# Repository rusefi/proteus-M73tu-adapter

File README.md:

# proteus-m73tu-adapter

Part of https://github.com/rusefi/rusefi/wiki/Proteus#adapters family

https://github.com/mck1117/proteus meets https://github.com/rusefi/rusefi/wiki/HOWTO-M73-v12-on-Proteus

V12 harness uses _TWO_ 134 pin connectors - one with BLACK plugs another with GREY plugs.

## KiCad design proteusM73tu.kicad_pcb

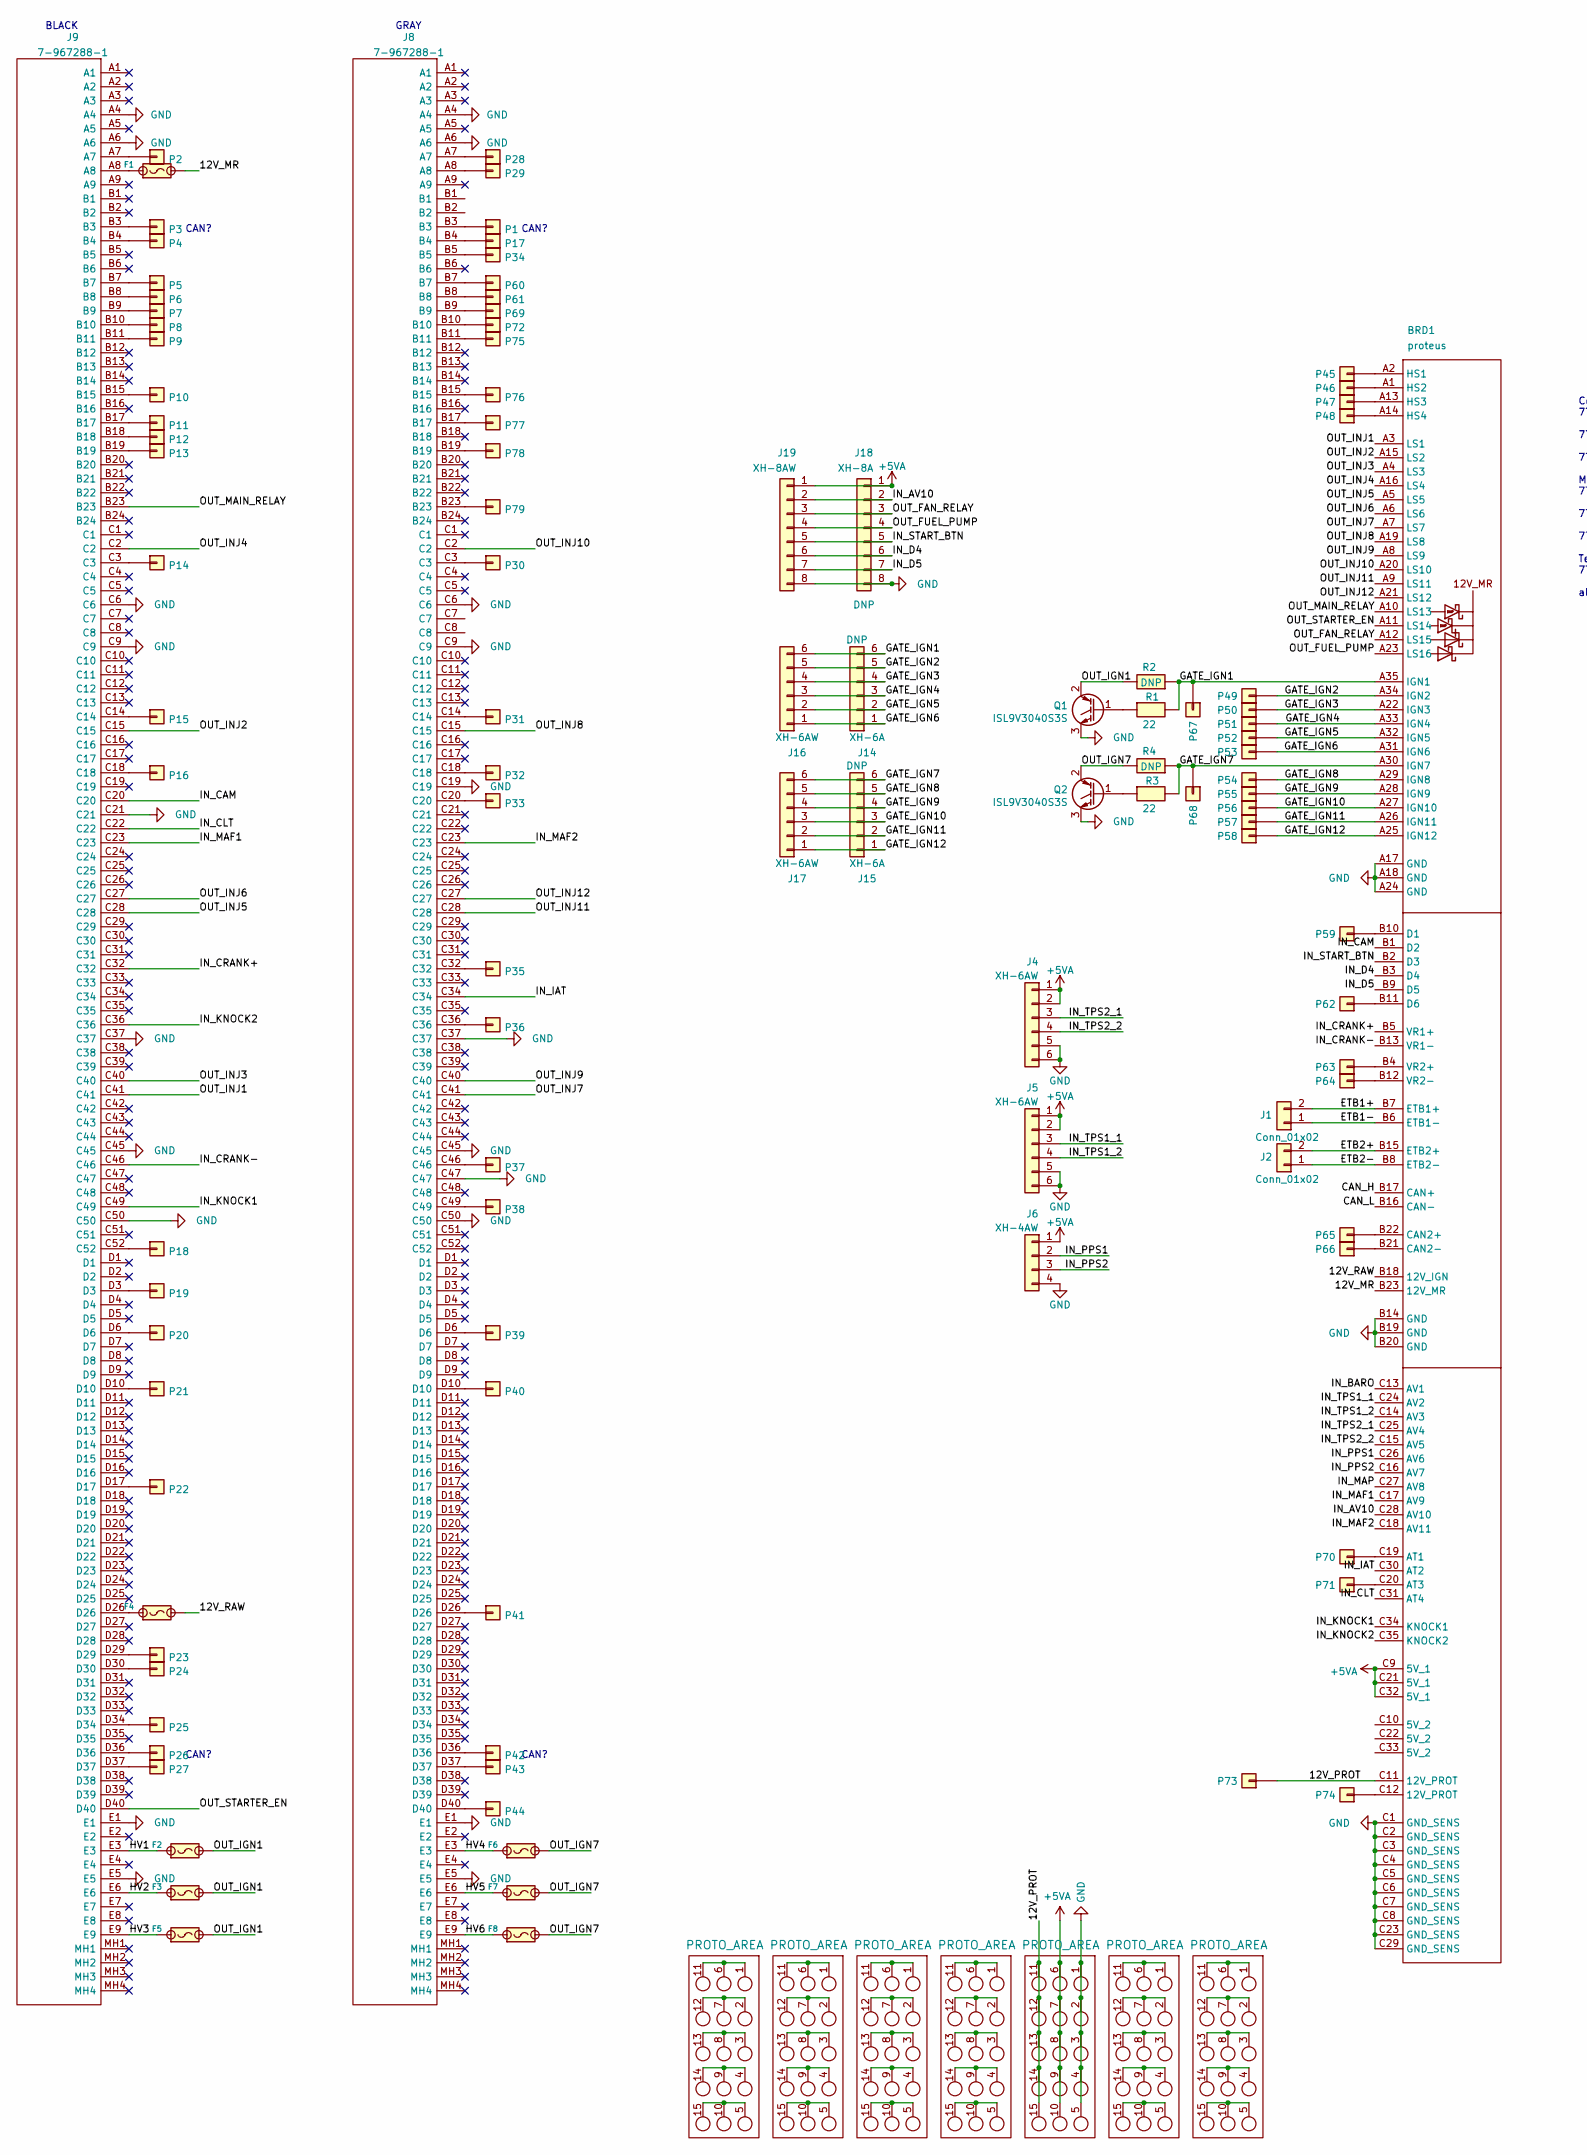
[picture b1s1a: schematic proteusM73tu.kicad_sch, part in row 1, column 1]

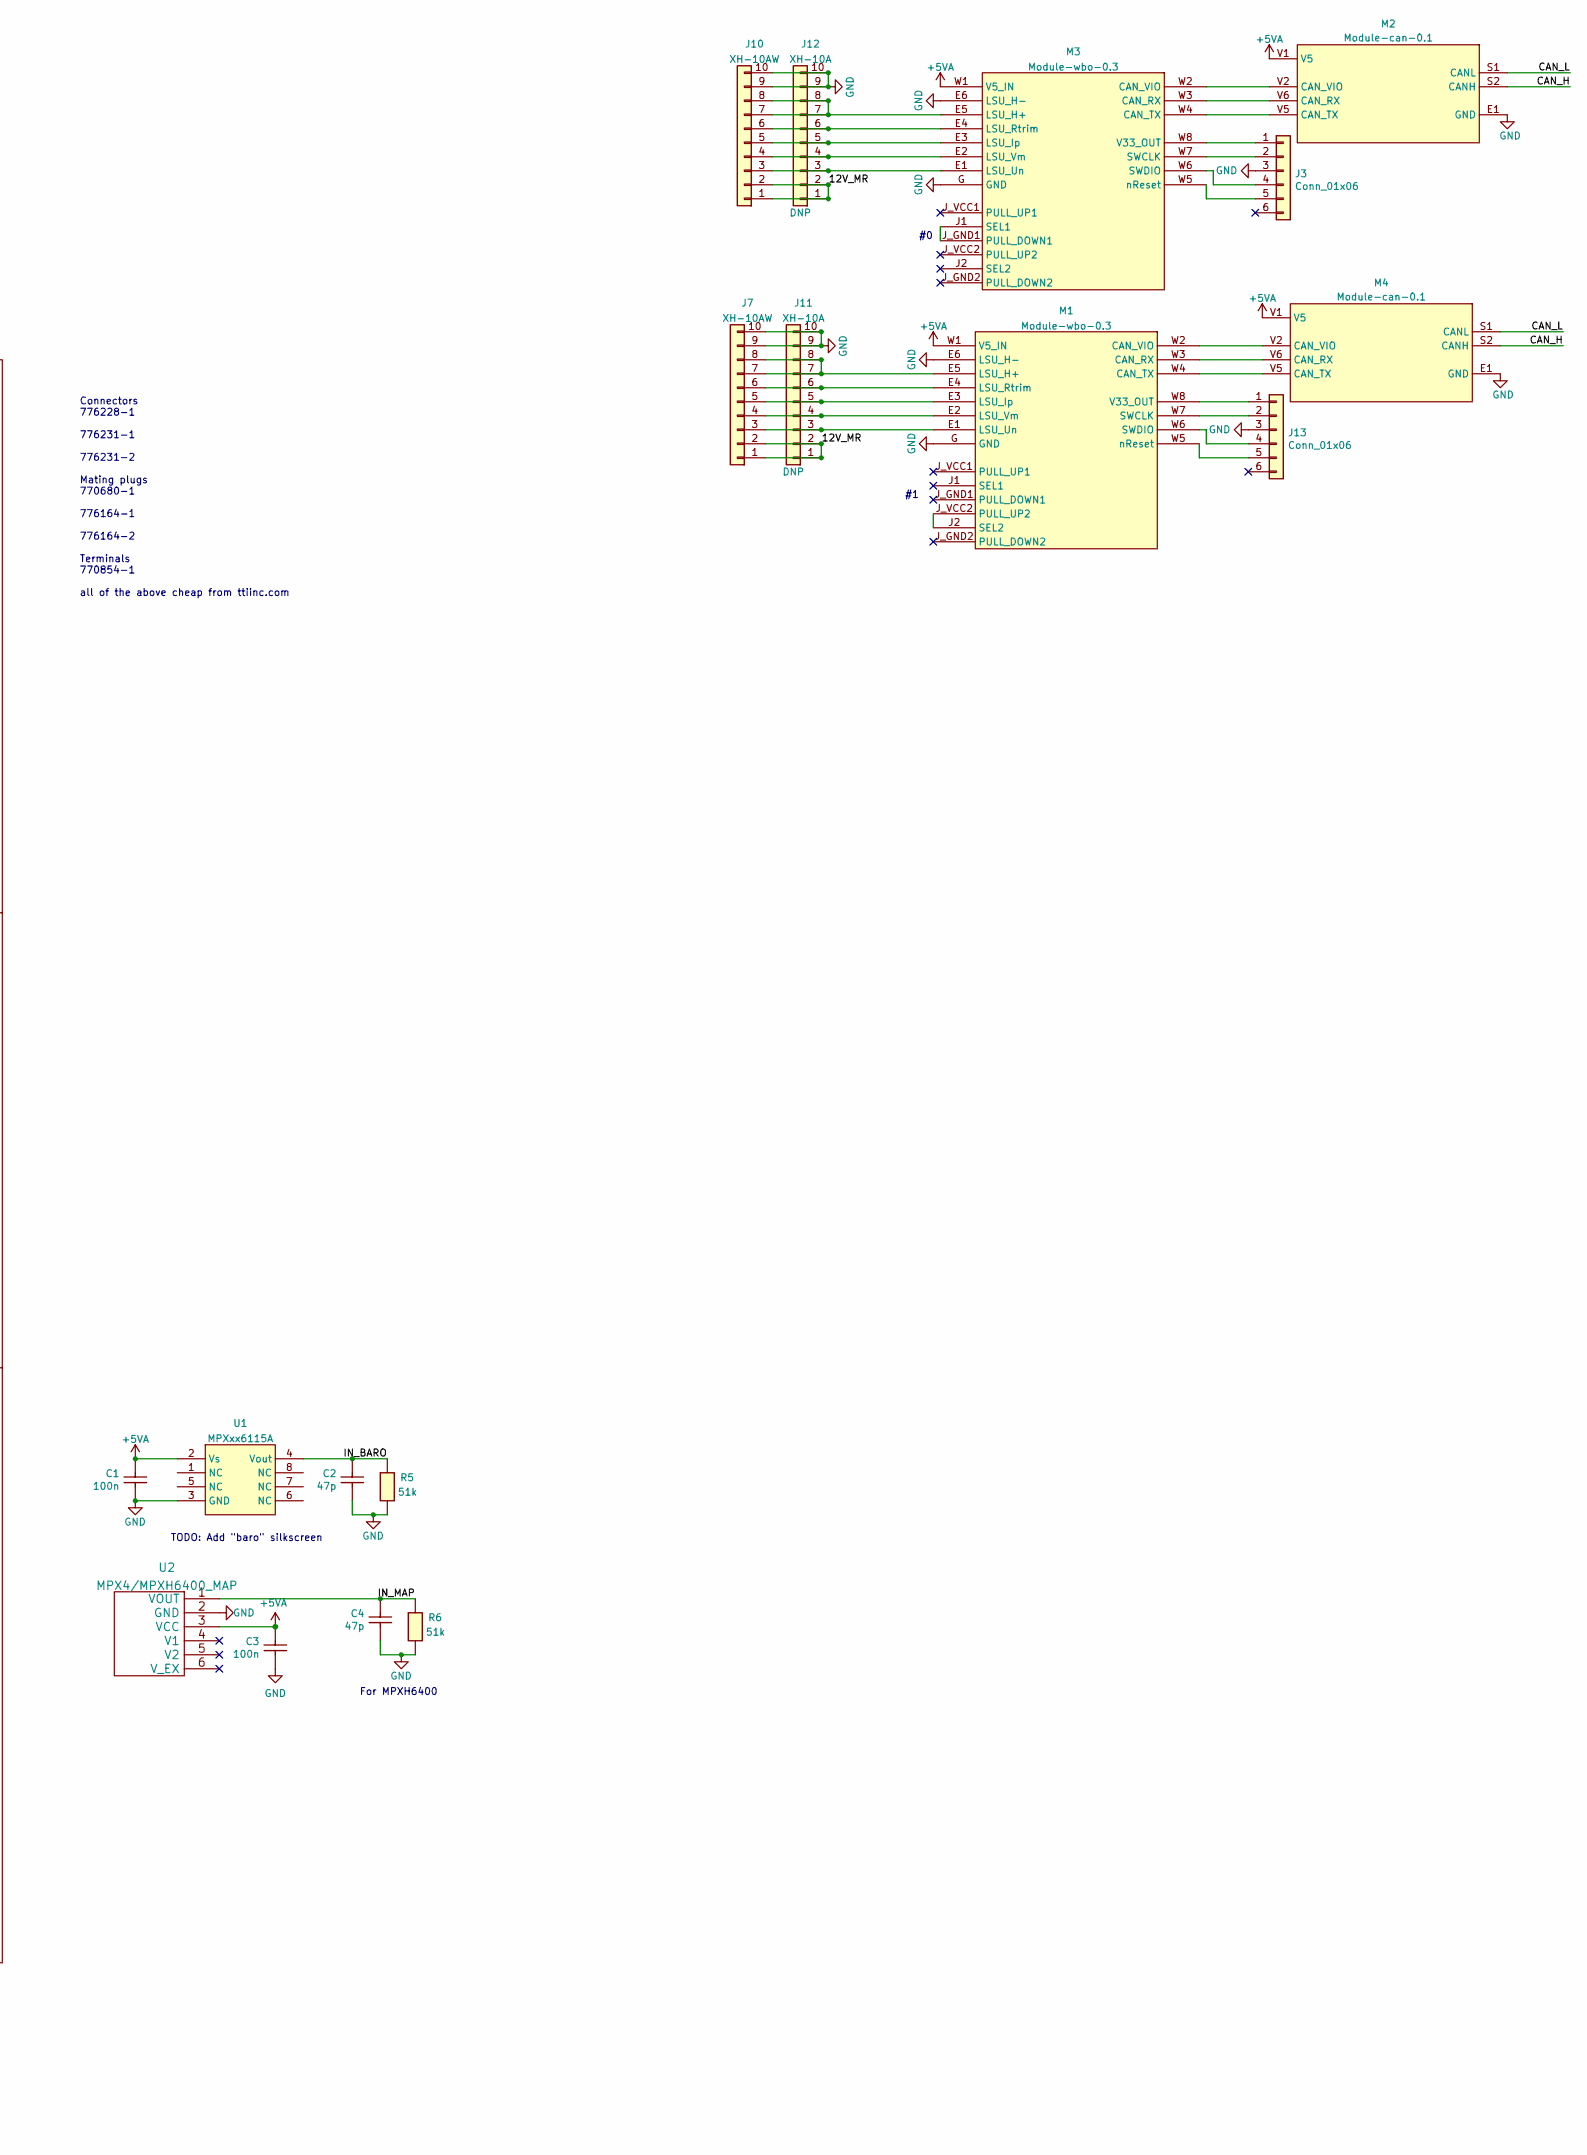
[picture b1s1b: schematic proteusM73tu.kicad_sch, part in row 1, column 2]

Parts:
BRD1: proteus
C1, C3: 100n; C0603; LCSC C14663
C2, C4: 47p; C0603; LCSC C1671
F1, F4: Fuse-Pad-Pad; PAD-1206-PAD; LCSC C182446
F2, F3, F5, F6, F7, F8: 10A; FUSE_8.5x4; LCSC C354908
G1, G2, G3, G4, G5, G6, G7: PROTO_AREA
J1, J2: Conn_01x02; Molex_Mini-Fit_Jr_5569-02A2_2x01_P4.20mm_Horizontal; LCSC C240832
J3, J13: Conn_01x06; PinHeader_1x06_P2.54mm_Vertical
J4, J5, J16, J17: XH-6AW; JST_XH_S6B-XH-A_1x06_P2.50mm_Horizontal; LCSC C8876
J6: XH-4AW; JST_XH_S4B-XH-A_1x04_P2.50mm_Horizontal; LCSC C21273
J7, J10: XH-10AW; JST_XH_S10B-XH-A_1x10_P2.50mm_Horizontal; LCSC C14652
J8, J9: 7-967288-1; TE_7-967288-1; Mouser Part Number 571-7-967288-1
J11, J12: XH-10A; JST_XH_B10B-XH-A_1x10_P2.50mm_Vertical; LCSC C8885
J14, J15: XH-6A; JST_XH_B6B-XH-A_1x06_P2.50mm_Vertical; LCSC C5663
J18: XH-8A; JST_XH_B8B-XH-A_1x08_P2.50mm_Vertical; LCSC C10385
J19: XH-8AW; JST_XH_S8B-XH-A_1x08_P2.50mm_Horizontal; LCSC XH-8AW
M1, M3: Module-wbo-0.3; wbo
M2, M4: Module-can-0.1; can
P1, P2, P3, P4, P5, P6, P7, P8, P9, P10, P11, P12, P13, P14, P15, P16, P17, P18, P19, P20, P21, P22, P23, P24, P25, P26, P27, P28, P29, P30, P31, P32, P33, P34, P35, P36, P37, P38, P39, P40, P41, P42, P43, P44, P45, P46, P47, P48, P49, P50, P51, P52, P53, P54, P55, P56, P57, P58, P59, P60, P61, P62, P63, P64, P65, P66, P67, P68, P69, P70, P71, P72, P73, P74, P75, P76, P77, P78, P79: Pad; PAD-TH
Q1, Q2: ISL9V3040S3S; TO-263-2; LCSC C898702
R1, R3: 22; R0603; LCSC C23345
R2, R4: DNP; R_2512_6332Metric
R5, R6: 51k; R0603; LCSC C23196
U1: MPXxx6115A; MPX_SOP_SSOP
U2: MPX4/MPXH6400_MAP; MPX-4_MAP

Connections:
+5VA: BRD1.C9 (5V_1), BRD1.C21 (5V_1), BRD1.C32 (5V_1), C1.2, C3.2, G5.6, G5.7, G5.8, G5.9, G5.10, J4.1, J4.2, J5.1, J5.2, J6.1, J18.1, J19.1, M1.W1 (V5_IN), M2.V1 (V5), M3.W1 (V5_IN), M4.V1 (V5), U1.2 (Vs), U2.3 (VCC)
/12V_MR: BRD1.B23 (12V_MR), F1.2, J7.1, J7.2, J10.1, J10.2, J11.1, J11.2, J12.1, J12.2
/12V_PROT: BRD1.C11 (12V_PROT), G5.11, G5.12, G5.13, G5.14, G5.15, P73.1
/12V_RAW: BRD1.B18 (12V_IGN), F4.2
/CAN_H: BRD1.B17 (CAN+), M2.S2 (CANH), M4.S2 (CANH)
/CAN_L: BRD1.B16 (CAN-), M2.S1 (CANL), M4.S1 (CANL)
/ETB1+: BRD1.B7 (ETB1+), J1.2
/ETB1-: BRD1.B6 (ETB1-), J1.1
/ETB2+: BRD1.B15 (ETB2+), J2.2
/ETB2-: BRD1.B8 (ETB2-), J2.1
/GATE_IGN1: BRD1.A35 (IGN1), J14.6, J16.6, P67.1, R1.2, R2.1
/GATE_IGN2: BRD1.A34 (IGN2), J14.5, J16.5, P49.1
/GATE_IGN3: BRD1.A22 (IGN3), J14.4, J16.4, P50.1
/GATE_IGN4: BRD1.A33 (IGN4), J14.3, J16.3, P51.1
/GATE_IGN5: BRD1.A32 (IGN5), J14.2, J16.2, P52.1
/GATE_IGN6: BRD1.A31 (IGN6), J14.1, J16.1, P53.1
/GATE_IGN7: BRD1.A30 (IGN7), J15.6, J17.6, P68.1, R3.2, R4.1
/GATE_IGN8: BRD1.A29 (IGN8), J15.5, J17.5, P54.1
/GATE_IGN9: BRD1.A28 (IGN9), J15.4, J17.4, P55.1
/GATE_IGN10: BRD1.A27 (IGN10), J15.3, J17.3, P56.1
/GATE_IGN11: BRD1.A26 (IGN11), J15.2, J17.2, P57.1
/GATE_IGN12: BRD1.A25 (IGN12), J15.1, J17.1, P58.1
/HV1: F2.1, J9.E3
/HV2: F3.1, J9.E6
/HV3: F5.1, J9.E9
/HV4: F6.1, J8.E3
/HV5: F7.1, J8.E6
/HV6: F8.1, J8.E9
/IN_AV10: BRD1.C28 (AV10), J18.2, J19.2
/IN_BARO: BRD1.C13 (AV1), C2.2, R5.1, U1.4 (Vout)
/IN_CAM: BRD1.B1 (D2), J9.C20
/IN_CLT: BRD1.C31 (AT4), J9.C22
/IN_CRANK+: BRD1.B5 (VR1+), J9.C32
/IN_CRANK-: BRD1.B13 (VR1-), J9.C46
/IN_D4: BRD1.B3 (D4), J18.6, J19.6
/IN_D5: BRD1.B9 (D5), J18.7, J19.7
/IN_IAT: BRD1.C30 (AT2), J8.C34
/IN_KNOCK1: BRD1.C34 (KNOCK1), J9.C49
/IN_KNOCK2: BRD1.C35 (KNOCK2), J9.C36
/IN_MAF1: BRD1.C17 (AV9), J9.C23
/IN_MAF2: BRD1.C18 (AV11), J8.C23
/IN_MAP: BRD1.C27 (AV8), C4.2, R6.1, U2.1 (VOUT)
/IN_PPS1: BRD1.C26 (AV6), J6.2
/IN_PPS2: BRD1.C16 (AV7), J6.3
/IN_START_BTN: BRD1.B2 (D3), J18.5, J19.5
/IN_TPS1_1: BRD1.C24 (AV2), J5.3
/IN_TPS1_2: BRD1.C14 (AV3), J5.4
/IN_TPS2_1: BRD1.C25 (AV4), J4.3
/IN_TPS2_2: BRD1.C15 (AV5), J4.4
/OUT_FAN_RELAY: BRD1.A12 (LS15), J18.3, J19.3
/OUT_FUEL_PUMP: BRD1.A23 (LS16), J18.4, J19.4
/OUT_IGN1: F2.2, F3.2, F5.2, Q1.2 (C), R2.2
/OUT_IGN7: F6.2, F7.2, F8.2, Q2.2 (C), R4.2
/OUT_INJ1: BRD1.A3 (LS1), J9.C41
/OUT_INJ2: BRD1.A15 (LS2), J9.C15
/OUT_INJ3: BRD1.A4 (LS3), J9.C40
/OUT_INJ4: BRD1.A16 (LS4), J9.C2
/OUT_INJ5: BRD1.A5 (LS5), J9.C28
/OUT_INJ6: BRD1.A6 (LS6), J9.C27
/OUT_INJ7: BRD1.A7 (LS7), J8.C41
/OUT_INJ8: BRD1.A19 (LS8), J8.C15
/OUT_INJ9: BRD1.A8 (LS9), J8.C40
/OUT_INJ10: BRD1.A20 (LS10), J8.C2
/OUT_INJ11: BRD1.A9 (LS11), J8.C28
/OUT_INJ12: BRD1.A21 (LS12), J8.C27
/OUT_MAIN_RELAY: BRD1.A10 (LS13), J9.B23
/OUT_STARTER_EN: BRD1.A11 (LS14), J9.D40
GND: BRD1.A17 (GND), BRD1.A18 (GND), BRD1.A24 (GND), BRD1.B14 (GND), BRD1.B19 (GND), BRD1.B20 (GND), BRD1.C1 (GND_SENS), BRD1.C2 (GND_SENS), BRD1.C3 (GND_SENS), BRD1.C4 (GND_SENS), BRD1.C5 (GND_SENS), BRD1.C6 (GND_SENS), BRD1.C7 (GND_SENS), BRD1.C8 (GND_SENS), BRD1.C23 (GND_SENS), BRD1.C29 (GND_SENS), C1.1, C2.1, C3.1, C4.1, G5.1, G5.2, G5.3, G5.4, G5.5, J3.3, J4.5, J4.6, J5.5, J5.6, J6.4, J7.9, J7.10, J8.A4, J8.A6, J8.C6, J8.C9, J8.C19, J8.C37, J8.C45, J8.C47, J8.C50, J8.E1, J8.E5, J9.A4, J9.A6, J9.C6, J9.C9, J9.C21, J9.C37, J9.C45, J9.C50, J9.E1, J9.E5, J10.9, J10.10, J11.9, J11.10, J12.9, J12.10, J13.3, J18.8, J19.8, M1.E6 (LSU_H-), M1.G (GND), M2.E1 (GND), M3.E6 (LSU_H-), M3.G (GND), M4.E1 (GND), Q1.3 (E), Q2.3 (E), R5.2, R6.2, U1.3 (GND), U2.2 (GND)
unnamed: BRD1.A1 (HS2), P46.1
unnamed: BRD1.A2 (HS1), P45.1
unnamed: BRD1.A13 (HS3), P47.1
unnamed: BRD1.A14 (HS4), P48.1
unnamed: BRD1.B4 (VR2+), P63.1
unnamed: BRD1.B10 (D1), P59.1
unnamed: BRD1.B11 (D6), P62.1
unnamed: BRD1.B12 (VR2-), P64.1
unnamed: BRD1.B21 (CAN2-), P66.1
unnamed: BRD1.B22 (CAN2+), P65.1
unnamed: BRD1.C12 (12V_PROT), P74.1
unnamed: BRD1.C19 (AT1), P70.1
unnamed: BRD1.C20 (AT3), P71.1
unnamed: F1.1, J9.A8
unnamed: F4.1, J9.D26
unnamed: G1.1, G1.6, G1.11
unnamed: G1.5, G1.10, G1.15
unnamed: G1.2, G1.7, G1.12
unnamed: G1.3, G1.8, G1.13
unnamed: G1.4, G1.9, G1.14
unnamed: G2.1, G2.6, G2.11
unnamed: G2.5, G2.10, G2.15
unnamed: G2.2, G2.7, G2.12
unnamed: G2.3, G2.8, G2.13
unnamed: G2.4, G2.9, G2.14
unnamed: G3.1, G3.6, G3.11
unnamed: G3.5, G3.10, G3.15
unnamed: G3.2, G3.7, G3.12
unnamed: G3.3, G3.8, G3.13
unnamed: G3.4, G3.9, G3.14
unnamed: G4.1, G4.6, G4.11
unnamed: G4.5, G4.10, G4.15
unnamed: G4.2, G4.7, G4.12
unnamed: G4.3, G4.8, G4.13
unnamed: G4.4, G4.9, G4.14
unnamed: G6.1, G6.6, G6.11
unnamed: G6.5, G6.10, G6.15
unnamed: G6.2, G6.7, G6.12
unnamed: G6.3, G6.8, G6.13
unnamed: G6.4, G6.9, G6.14
unnamed: G7.1, G7.6, G7.11
unnamed: G7.5, G7.10, G7.15
unnamed: G7.2, G7.7, G7.12
unnamed: G7.3, G7.8, G7.13
unnamed: G7.4, G7.9, G7.14
unnamed: J3.1, M3.W8 (V33_OUT)
unnamed: J3.2, M3.W7 (SWCLK)
unnamed: J3.4, M3.W6 (SWDIO)
unnamed: J3.5, M3.W5 (nReset)
unnamed: J8.A7, P28.1
unnamed: J8.A8, P29.1
unnamed: J8.B3, P1.1
unnamed: J8.B4, P17.1
unnamed: J8.B5, P34.1
unnamed: J8.B7, P60.1
unnamed: J8.B8, P61.1
unnamed: J8.B9, P69.1
unnamed: J8.B10, P72.1
unnamed: J8.B11, P75.1
unnamed: J8.B15, P76.1
unnamed: J8.B17, P77.1
unnamed: J8.B19, P78.1
unnamed: J8.B23, P79.1
unnamed: J8.C3, P30.1
unnamed: J8.C14, P31.1
unnamed: J8.C18, P32.1
unnamed: J8.C20, P33.1
unnamed: J8.C32, P35.1
unnamed: J8.C36, P36.1
unnamed: J8.C46, P37.1
unnamed: J8.C49, P38.1
unnamed: J8.D6, P39.1
unnamed: J8.D10, P40.1
unnamed: J8.D26, P41.1
unnamed: J8.D36, P42.1
unnamed: J8.D37, P43.1
unnamed: J8.D40, P44.1
unnamed: J9.A7, P2.1
unnamed: J9.B3, P3.1
unnamed: J9.B4, P4.1
unnamed: J9.B7, P5.1
unnamed: J9.B8, P6.1
unnamed: J9.B9, P7.1
unnamed: J9.B10, P8.1
unnamed: J9.B11, P9.1
unnamed: J9.B15, P10.1
unnamed: J9.B17, P11.1
unnamed: J9.B18, P12.1
unnamed: J9.B19, P13.1
unnamed: J9.C3, P14.1
unnamed: J9.C14, P15.1
unnamed: J9.C18, P16.1
unnamed: J9.C52, P18.1
unnamed: J9.D3, P19.1
unnamed: J9.D6, P20.1
unnamed: J9.D10, P21.1
unnamed: J9.D17, P22.1
unnamed: J9.D29, P23.1
unnamed: J9.D30, P24.1
unnamed: J9.D34, P25.1
unnamed: J9.D36, P26.1
unnamed: J9.D37, P27.1
unnamed: J10.3, J12.3, M3.E1 (LSU_Un)
unnamed: J10.4, J12.4, M3.E2 (LSU_Vm)
unnamed: J10.5, J12.5, M3.E3 (LSU_Ip)
unnamed: J10.6, J12.6, M3.E4 (LSU_Rtrim)
unnamed: J10.7, J10.8, J12.7, J12.8, M3.E5 (LSU_H+)
unnamed: J7.3, J11.3, M1.E1 (LSU_Un)
unnamed: J7.4, J11.4, M1.E2 (LSU_Vm)
unnamed: J7.5, J11.5, M1.E3 (LSU_Ip)
unnamed: J7.6, J11.6, M1.E4 (LSU_Rtrim)
unnamed: J7.7, J7.8, J11.7, J11.8, M1.E5 (LSU_H+)
unnamed: J13.1, M1.W8 (V33_OUT)
unnamed: J13.2, M1.W7 (SWCLK)
unnamed: J13.4, M1.W6 (SWDIO)
unnamed: J13.5, M1.W5 (nReset)
unnamed: M1.J2 (SEL2), M1.J_VCC2 (PULL_UP2)
unnamed: M1.W2 (CAN_VIO), M4.V2 (CAN_VIO)
unnamed: M1.W3 (CAN_RX), M4.V6 (CAN_RX)
unnamed: M1.W4 (CAN_TX), M4.V5 (CAN_TX)
unnamed: M2.V2 (CAN_VIO), M3.W2 (CAN_VIO)
unnamed: M2.V5 (CAN_TX), M3.W4 (CAN_TX)
unnamed: M2.V6 (CAN_RX), M3.W3 (CAN_RX)
unnamed: M3.J1 (SEL1), M3.J_GND1 (PULL_DOWN1)
unnamed: Q1.1 (G), R1.1
unnamed: Q2.1 (G), R3.1

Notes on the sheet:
BLACK
CAN?
GRAY
Connectors 776228-1 776231-1 776231-2 Mating plugs 770680-1 776164-1 776164-2 Terminals 770854-1 all of the above cheap from ttiinc.com
TODO: Add "baro" silkscreen
For MPXH6400

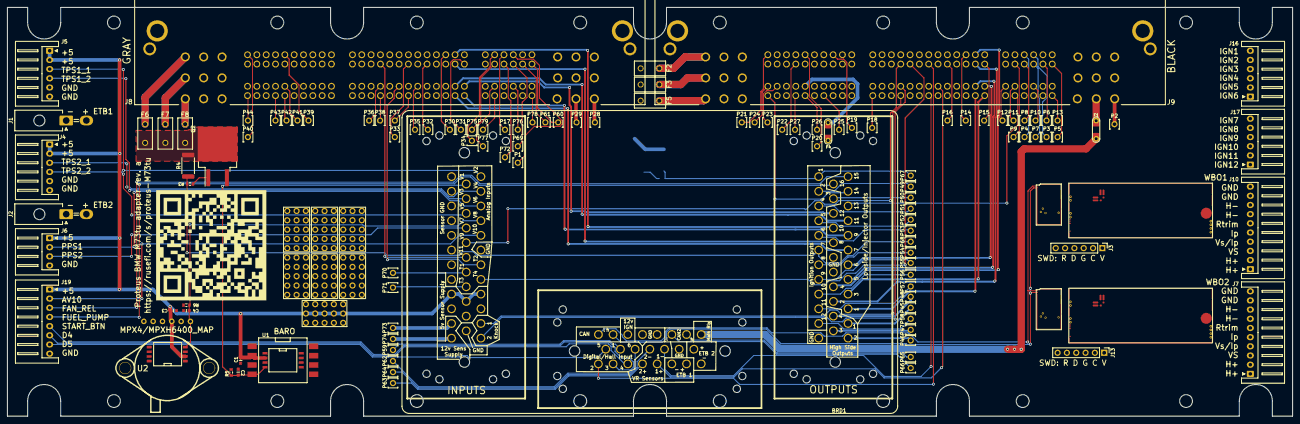
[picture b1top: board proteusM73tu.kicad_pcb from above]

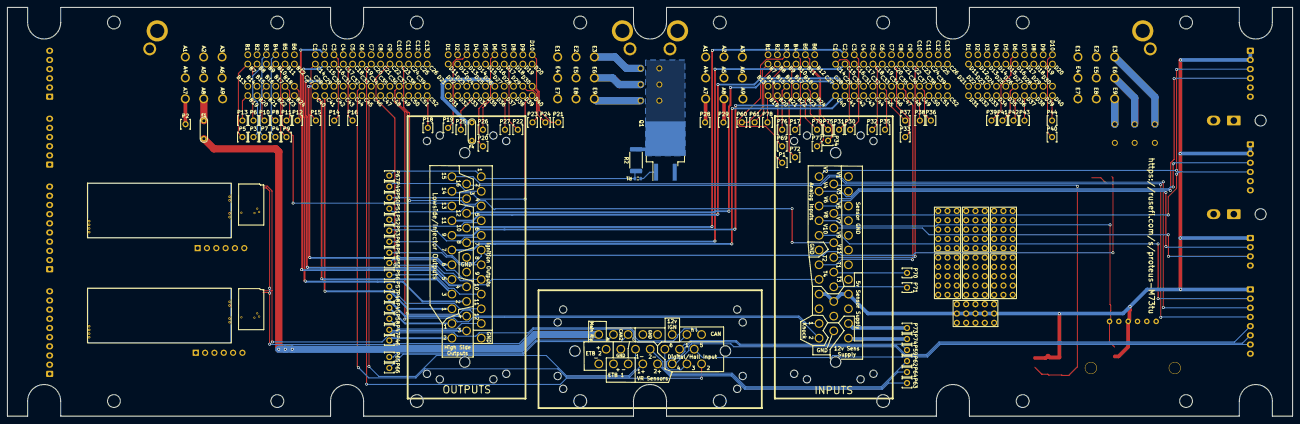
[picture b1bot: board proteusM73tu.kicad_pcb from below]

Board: 2 copper layers, 350.0 x 111.3 mm, 127 parts (3 on the bottom side), 194 nets.

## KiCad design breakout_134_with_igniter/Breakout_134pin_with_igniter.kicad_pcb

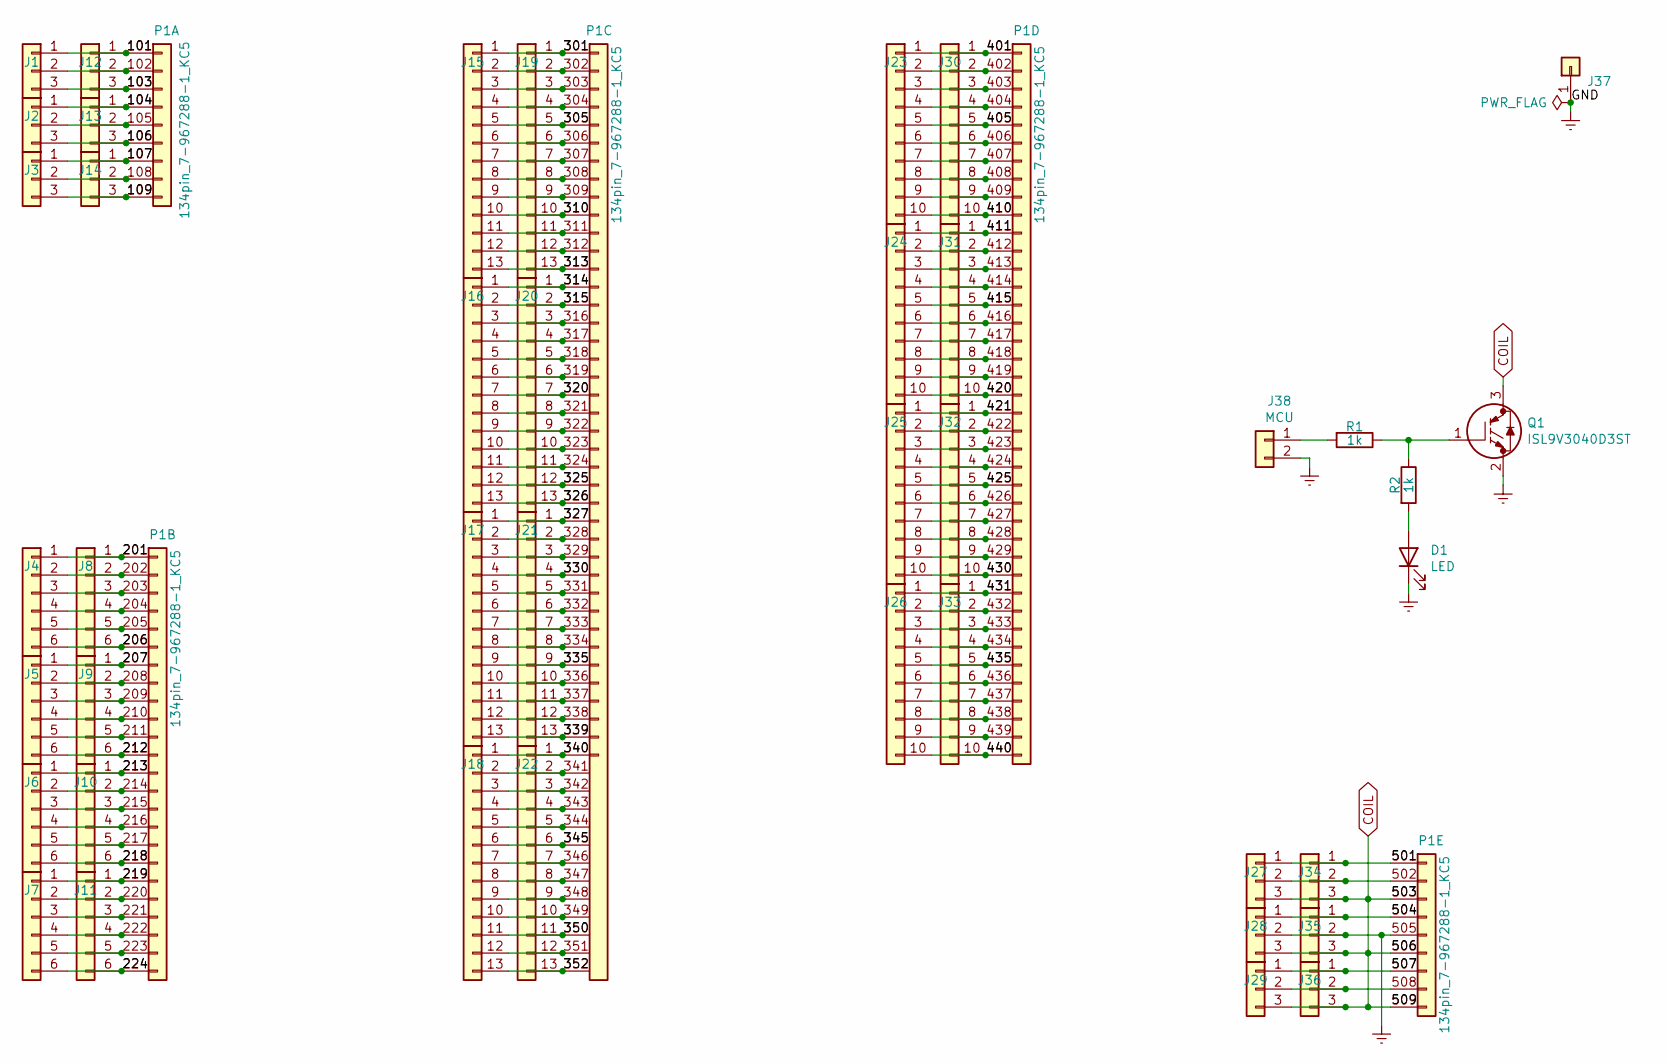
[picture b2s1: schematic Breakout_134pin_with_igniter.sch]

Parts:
D1: LED; LED_0603; Jlcpcb Part Number C205443
J1, J2, J3, J12, J13, J14, J27, J28, J29, J34, J35, J36: Conn_01x03; G_03x5.08mm
J4, J5, J6, J7, J8, J9, J10, J11: Conn_01x06; Pin_Header_Straight_1x06_Pitch2.54mm
J15, J16, J17, J18, J19, J20, J21, J22: Conn_01x13; Pin_Header_Straight_1x13_Pitch2.54mm
J23, J24, J25, J26, J30, J31, J32, J33: Conn_01x10; Pin_Header_Straight_1x10_Pitch2.54mm
J37: Conn_01x01; Pin_Header_Straight_1x01_Pitch2.54mm
J38: MCU; Pin_Header_Straight_1x02_Pitch2.54mm
P1: 134pin_7-967288-1_KC5; 7-967288-1_134-pin-connector
Q1: ISL9V3040D3ST; Manufacturer_Part_Number ISL9V3040D3ST; Mouser Part Number 512-ISL9V3040D3ST
R1, R2: 1k; R_0603; Jlcpcb Part Number C21190

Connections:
/101: J1.1, J12.1, P1.101
/103: J1.3, J12.3, P1.103
/104: J2.1, J13.1, P1.104
/106: J2.3, J13.3, P1.106
/107: J3.1, J14.1, P1.107
/109: J3.3, J14.3, P1.109
/201: J4.1, J8.1, P1.201
/206: J4.6, J8.6, P1.206
/207: J5.1, J9.1, P1.207
/212: J5.6, J9.6, P1.212
/213: J6.1, J10.1, P1.213
/218: J6.6, J10.6, P1.218
/219: J7.1, J11.1, P1.219
/224: J7.6, J11.6, P1.224
/301: J15.1, J19.1, P1.301
/305: J15.5, J19.5, P1.305
/310: J15.10, J19.10, P1.310
/313: J15.13, J19.13, P1.313
/314: J16.1, J20.1, P1.314
/315: J16.2, J20.2, P1.315
/320: J16.7, J20.7, P1.320
/325: J16.12, J20.12, P1.325
/326: J16.13, J20.13, P1.326
/327: J17.1, J21.1, P1.327
/330: J17.4, J21.4, P1.330
/335: J17.9, J21.9, P1.335
/339: J17.13, J21.13, P1.339
/340: J18.1, J22.1, P1.340
/345: J18.6, J22.6, P1.345
/350: J18.11, J22.11, P1.350
/352: J18.13, J22.13, P1.352
/401: J23.1, J30.1, P1.401
/405: J23.5, J30.5, P1.405
/410: J23.10, J30.10, P1.410
/411: J24.1, J31.1, P1.411
/415: J24.5, J31.5, P1.415
/420: J24.10, J31.10, P1.420
/421: J25.1, J32.1, P1.421
/425: J25.5, J32.5, P1.425
/430: J25.10, J32.10, P1.430
/431: J26.1, J33.1, P1.431
/435: J26.5, J33.5, P1.435
/440: J26.10, J33.10, P1.440
/501: J27.1, J34.1, P1.501
/504: J28.1, J35.1, P1.504
/507: J29.1, J36.1, P1.507
COIL: J27.3, J28.3, J29.3, J34.3, J35.3, J36.3, P1.503, P1.506, P1.509, Q1.3
Earth: D1.1 (K), J28.2, J35.2, J37.1, J38.2, P1.505, Q1.2
unnamed: D1.2 (A), R2.2
unnamed: J1.2, J12.2, P1.102
unnamed: J4.2, J8.2, P1.202
unnamed: J4.3, J8.3, P1.203
unnamed: J4.4, J8.4, P1.204
unnamed: J4.5, J8.5, P1.205
unnamed: J5.2, J9.2, P1.208
unnamed: J5.3, J9.3, P1.209
unnamed: J5.4, J9.4, P1.210
unnamed: J5.5, J9.5, P1.211
unnamed: J6.2, J10.2, P1.214
unnamed: J6.3, J10.3, P1.215
unnamed: J6.4, J10.4, P1.216
unnamed: J6.5, J10.5, P1.217
unnamed: J7.2, J11.2, P1.220
unnamed: J7.3, J11.3, P1.221
unnamed: J7.4, J11.4, P1.222
unnamed: J7.5, J11.5, P1.223
unnamed: J2.2, J13.2, P1.105
unnamed: J3.2, J14.2, P1.108
unnamed: J15.2, J19.2, P1.302
unnamed: J15.3, J19.3, P1.303
unnamed: J15.4, J19.4, P1.304
unnamed: J15.6, J19.6, P1.306
unnamed: J15.7, J19.7, P1.307
unnamed: J15.8, J19.8, P1.308
unnamed: J15.9, J19.9, P1.309
unnamed: J15.11, J19.11, P1.311
unnamed: J15.12, J19.12, P1.312
unnamed: J16.3, J20.3, P1.316
unnamed: J16.4, J20.4, P1.317
unnamed: J16.5, J20.5, P1.318
unnamed: J16.6, J20.6, P1.319
unnamed: J16.8, J20.8, P1.321
unnamed: J16.9, J20.9, P1.322
unnamed: J16.10, J20.10, P1.323
unnamed: J16.11, J20.11, P1.324
unnamed: J17.2, J21.2, P1.328
unnamed: J17.3, J21.3, P1.329
unnamed: J17.5, J21.5, P1.331
unnamed: J17.6, J21.6, P1.332
unnamed: J17.7, J21.7, P1.333
unnamed: J17.8, J21.8, P1.334
unnamed: J17.10, J21.10, P1.336
unnamed: J17.11, J21.11, P1.337
unnamed: J17.12, J21.12, P1.338
unnamed: J18.2, J22.2, P1.341
unnamed: J18.3, J22.3, P1.342
unnamed: J18.4, J22.4, P1.343
unnamed: J18.5, J22.5, P1.344
unnamed: J18.7, J22.7, P1.346
unnamed: J18.8, J22.8, P1.347
unnamed: J18.9, J22.9, P1.348
unnamed: J18.10, J22.10, P1.349
unnamed: J18.12, J22.12, P1.351
unnamed: J23.2, J30.2, P1.402
unnamed: J23.3, J30.3, P1.403
unnamed: J23.4, J30.4, P1.404
unnamed: J23.6, J30.6, P1.406
unnamed: J23.7, J30.7, P1.407
unnamed: J23.8, J30.8, P1.408
unnamed: J23.9, J30.9, P1.409
unnamed: J24.2, J31.2, P1.412
unnamed: J24.3, J31.3, P1.413
unnamed: J24.4, J31.4, P1.414
unnamed: J24.6, J31.6, P1.416
unnamed: J24.7, J31.7, P1.417
unnamed: J24.8, J31.8, P1.418
unnamed: J24.9, J31.9, P1.419
unnamed: J25.2, J32.2, P1.422
unnamed: J25.3, J32.3, P1.423
unnamed: J25.4, J32.4, P1.424
unnamed: J25.6, J32.6, P1.426
unnamed: J25.7, J32.7, P1.427
unnamed: J25.8, J32.8, P1.428
unnamed: J25.9, J32.9, P1.429
unnamed: J26.2, J33.2, P1.432
unnamed: J26.3, J33.3, P1.433
unnamed: J26.4, J33.4, P1.434
unnamed: J26.6, J33.6, P1.436
unnamed: J26.7, J33.7, P1.437
unnamed: J26.8, J33.8, P1.438
unnamed: J26.9, J33.9, P1.439
unnamed: J27.2, J34.2, P1.502
unnamed: J29.2, J36.2, P1.508
unnamed: J38.1, R1.2
unnamed: Q1.1, R1.1, R2.1

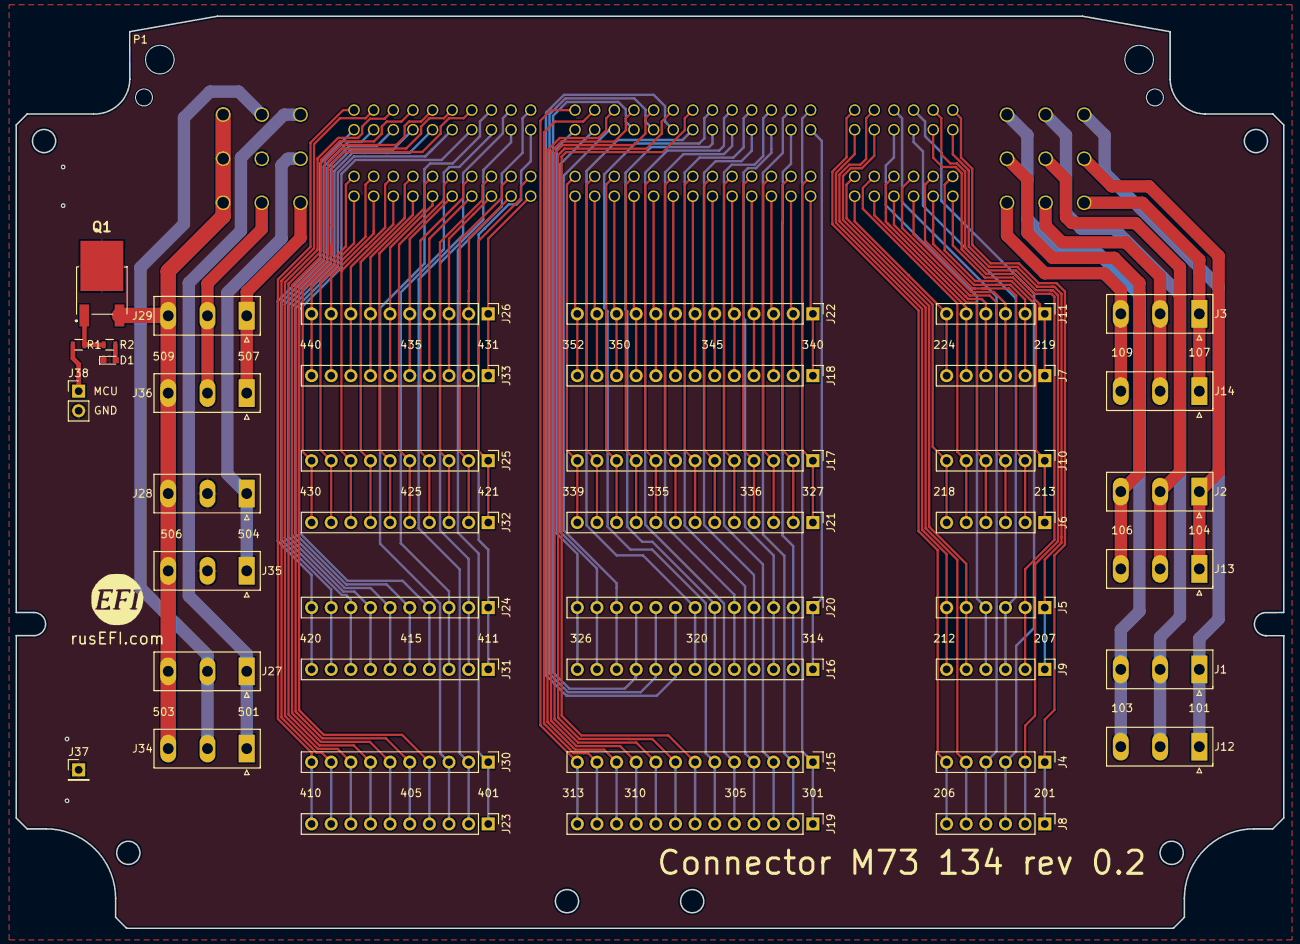
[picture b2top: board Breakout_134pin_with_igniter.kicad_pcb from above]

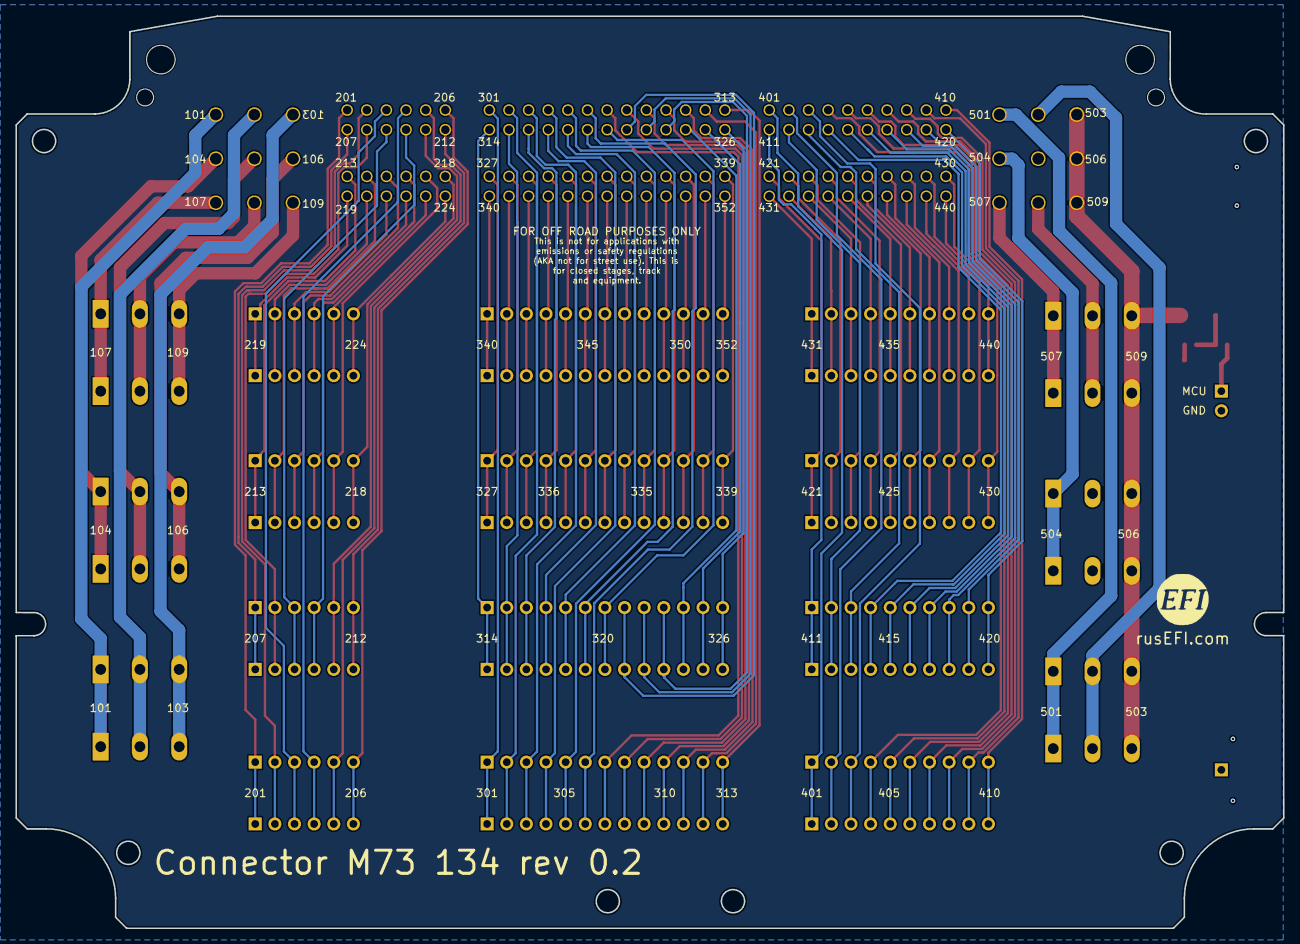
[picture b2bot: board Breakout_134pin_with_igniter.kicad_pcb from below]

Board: 2 copper layers, 164.0 x 118.0 mm, 46 parts (2 on the bottom side), 135 nets.

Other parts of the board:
G?: LOGO
G?#2: Disclaimer; Off_Road_Disclaimer
G?#3: LOGO

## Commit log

2021-09-21 proto
2021-09-21 random files
2021-09-26 Placed connectors
2021-09-27 Progress
2021-09-29 ETB pins drama
2021-10-04 Upd pinout
2021-10-04 Upd sch
2021-10-24 Upd PCB
2021-10-25 Fab preview
2021-10-26 dead stuff
2021-10-26 Board size
